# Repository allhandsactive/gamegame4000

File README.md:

# gameGame 4000
This is the *gameGame 4000*: an ESP8266-based, wifi-enabled "badge" learn-to-solder project designed for anyone who is interested in soldering on a somewhat intermediate level, or how to program these ubiquitous microcontrollers. Along with the ESP8266, it is equipped with an SSD1331 RGB OLED display, video game controller-alike buttons, and a small speaker for bleeps and bloops.  This kit is designed by *All Hands Active* (http://www.allhandsactive.org), a 501(c)(3) not-for-profit hackerspace (http://hackerspaces.org) located in Downtown Ann Arbor, MI, USA.  The included Arkanoid demo code here is based, almost verbatim, on code from the *ssd1331* library by Alexey Dynda (@lexus2k).  We added some tweaks to accommodate our unique button handling library, and adjusted pins to match our OLED screen setup.

As any good hackerspace should, we encourage people to fully tinker with the code and designs, and to find novel uses for this project.  We'd love to hear of your projects using our badge -- please get in contact with us if you'd like to share your project!

Since it is based on the same processor, much of this documentation is copied over from our last kit, the *mktwo* badge (https://github.com/allhandsactive/mktwo-badge/blob/master/README.md)

# Build instructions on Imgur
Heads up! There are a few errors in the assembly pictures at the imgur link here.  Please follow the instructions in the captions first and foremost: https://imgur.com/gallery/5YhMqiV

### **Kit parts list**

Make sure you have the following in your kit:

1x gameGame 4000 PCB

1x ESP8266 12E or 12F microprocessor

1x SSD1331 OLED display

1x 3-AA battery holder

1x Female battery connector lead with pigtail

1x Male battery connector header

1x Toggle switch

1x Header 7-socket

1x Right-angle header 6-pin

1x Speaker 8-ohm 20mm

1x Linear regulator 1.2A 3.3v STMicroelectronics P/N LDL1117S33R

1x Shift register 8-bit Nexperia USA Inc. P/N 74HC597D,653

2x Electrolytic capacitor 10uF 50V

2x Ceramic capacitor 0.1uF 50V

4x Nylon standoff M2 x 12mm

4x Nylon nut M2

4x Nylon screw M2 x 5mm

10x Push button

12x Resistor 10k Ohm 1/8W 5%

### **Requirements**
#### **Hardware**
The safest and more reliable way to load firmware onto your *gameGame 4000* is with a USB-serial programming cable.  You will need to use an FTDI cable, like the FTDI cable here (https://www.sparkfun.com/products/9717) , *OR* you can use a cheaper cable with the Prolific *PL2303HX* chipset (look on eBay! We were able to easily find them from US sellers for under $5).  A serial voltage level of 3.3v for programming is recommended, but we've safely done it with 5v, too.  **NOTE:** Windows/Apple users, you will likely have to download a driver to use the *PL2303HX*.  Sorry, we can't provide support on how to do that.

Such cables hook up to the FTDI pin block near the bottom of the *gameGame 4000*.  Take care when hooking up the cable, because the FTDI pins on the badge are not keyed.  When you plug it into the badge, make sure the black wire on the FTDI cable faces toward the left side of the badge (assuming you are viewing the front of the badge).  In case your cable doesn't have a single plug, but a bunch of individual wires (like the Prolific ones), the pinout should be as follows, assuming the board is facing up toward you, left-to-right (*NC = No Connection*):

**BLACK NC NC GREEN WHITE NC**

The red wire from the programming cable should not be connected, which also means you will need to power the badge with the battery when programming it.

#### **Software**
We recommend a current version of the Arduino IDE (https://www.arduino.cc/en/Main/Software), either binary or git clone.

Under Arduino's preferences, *Additional Boards Manager URLs*, you will need to add:

`http://arduino.esp8266.com/stable/package_esp8266com_index.json`

Under *Tools|Board:|Boards Manager...* search for and install `esp8266`.
**NOTE: you will need to add the URL above in preferences first.**
You will also need some libraries to run the OLED screen.  Under *Sketch|Include Library|Manage Libraries...* search for `SSD1331`.  Any of those should work to varying degrees.  Try them out and experiment! If you want to try the included `arkanoid8-pcon` demo, grab the `ssd1306` library, which comes with some cool demo stuff for our `SSD1331` OLED screen.  Keep in mind that you will have to update the pin settings on the other demos since they are connected differently for this board.

Now restart the Arduino IDE.

### **Badge Programming**
#### **Wired Programming**
##### **SETUP**

Under the Arduino IDE settings (most of these seem to be defaults):

Board: "NodeMCU 1.0 (ESP-12E Module)"

CPU Frequency: "80 MHz"

Debug Port: "Disabled"

Debug Level: "None"

lwIP Variant: "v2 Lower Memory"

Flash Size: "4M (3M SPIFFS)"

Upload Speed: "460800" (try lowering this if you have issues while programming the board)

Port: (whatever port the programming cable is on.  In Linux, it'll be something like `/dev/ttyUSB0`)

Programmer: "AVRISP mkII"

Erase Flash: "Only Sketch"

##### **PROCEDURE**

Let's take a look at the `ssd1306` library's demo games.  After installing that library, you can load up the `arkanoid8-gamegame` code from this repo.

To upload your code, you need to put the badge into "write" or "programming" mode.  To do this, locate the `PRGM` and `RESET` buttons on the badge.  Hold the `PRGM` button. Press and release the `RESET` button. You may now release `PRGM`. **You will need to repeat this procedure before each firmware upload.**
You may now compile and upload as you would with any Arduino, using the Arduino IDE.

**NOTE: Some FTDI cables might not cause the ESP to reset after successful programming.  If you are observing this behavior, just use the** `RESET` **button on the badge.**

### Other notes
The speaker is linked to pin 5, if you wish to make bleeps and bloops with the `tone` function.

Other pin settings that might be useful:

For the OLED display:

sclk = 14

mosi = 13

cs = 2

rst = 0

dc = 16

For buttons (check out the example code in this repo):

pl/sload = 4

shcp/sck = 0

stcp/clk = 15

shift reg. serial output ("BUTTONS" on schematic) = 10

The board works great with three NiMH AA batteries.

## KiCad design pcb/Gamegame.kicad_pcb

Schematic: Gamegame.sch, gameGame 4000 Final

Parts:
BT1: Battery; PinHeader_1x02_P2.54mm_Vertical
C1, C2: 0.1uF; C_Rect_L4.6mm_W2.0mm_P2.50mm_MKS02_FKP02
C3, C4: 10uF; C_Rect_L4.6mm_W2.0mm_P2.50mm_MKS02_FKP02
J1: FTDI; PinHeader_1x06_P2.54mm_Horizontal
J2: SSD1331 SPI OLED; SD1131
LS1: Speaker; PinHeader_1x02_P2.54mm_Vertical
R1, R2, R3, R4, R5, R6, R7, R8, R9, R10, R12, R13: 10k; R_Axial_DIN0204_L3.6mm_D1.6mm_P5.08mm_Horizontal
SW1: UP; SW_PUSH_6mm
SW2: DOWN; SW_PUSH_6mm
SW3: LEFT; SW_PUSH_6mm
SW4: RIGHT; SW_PUSH_6mm
SW5: A; SW_PUSH_6mm
SW6: B; SW_PUSH_6mm
SW7: START; SW_PUSH_6mm
SW8: SELECT; SW_PUSH_6mm
SW9: RESET; SW_PUSH_6mm
SW10: PRGM; SW_PUSH_6mm
SW11: SW_SPDT; FanPinHeader_1x03_P2.54mm_Vertical
U1: 74LS597; SOIC-16_3.9x9.9mm_P1.27mm
U2: ESP-12E
U3: AP1117-33; SOT-223-3_TabPin2

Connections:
+3V3: C1.1, C2.1, C4.1, J2.2, J2.5, R9.1, R10.1, R13.2, SW1.1, SW2.1, SW3.1, SW4.1, SW5.1, SW6.1, SW7.1, SW8.1, U1.10, U1.16, U2.8 (VCC), U3.2 (VO)
+BATT: C3.1, SW11.1, U3.3 (VI)
/BUTTONS: U1.9, U2.12 (GPIO10)
/CLK: J2.3, U2.5 (GPIO14)
/CS: J2.7, R13.1, U2.17 (GPIO2)
/DC: J2.6, U2.4 (GPIO16)
/MOSI: J2.4, U2.7 (GPIO13)
/RST: R10.2, SW9.2, U2.1 (REST)
/RX: J1.4, U2.21 (RXD)
/SHCP: SW10.1, U1.11, U2.18 (GPIO0)
/SPEAKER: LS1.1, U2.20 (GPIO5)
/STCP: R12.1, U1.12, U2.16 (GPIO15)
/TX: J1.5, U2.22 (TXD)
/~PL: U1.13, U2.19 (GPIO4)
GND: BT1.2, C1.2, C2.2, C3.2, C4.2, J1.1, J2.1, LS1.2, R1.2, R2.2, R3.2, R4.2, R5.2, R6.2, R7.2, R8.2, R12.2, SW9.1, SW10.2, U1.8, U1.14, U2.15 (GND), U3.1 (GND)
unnamed: BT1.1, SW11.2
unnamed: R1.1, SW1.2, U1.15
unnamed: R2.1, SW2.2, U1.1
unnamed: R3.1, SW3.2, U1.2
unnamed: R4.1, SW4.2, U1.3
unnamed: R5.1, SW5.2, U1.4
unnamed: R6.1, SW6.2, U1.5
unnamed: R7.1, SW7.2, U1.6
unnamed: R8.1, SW8.2, U1.7
unnamed: R9.2, U2.3 (CH_PD)

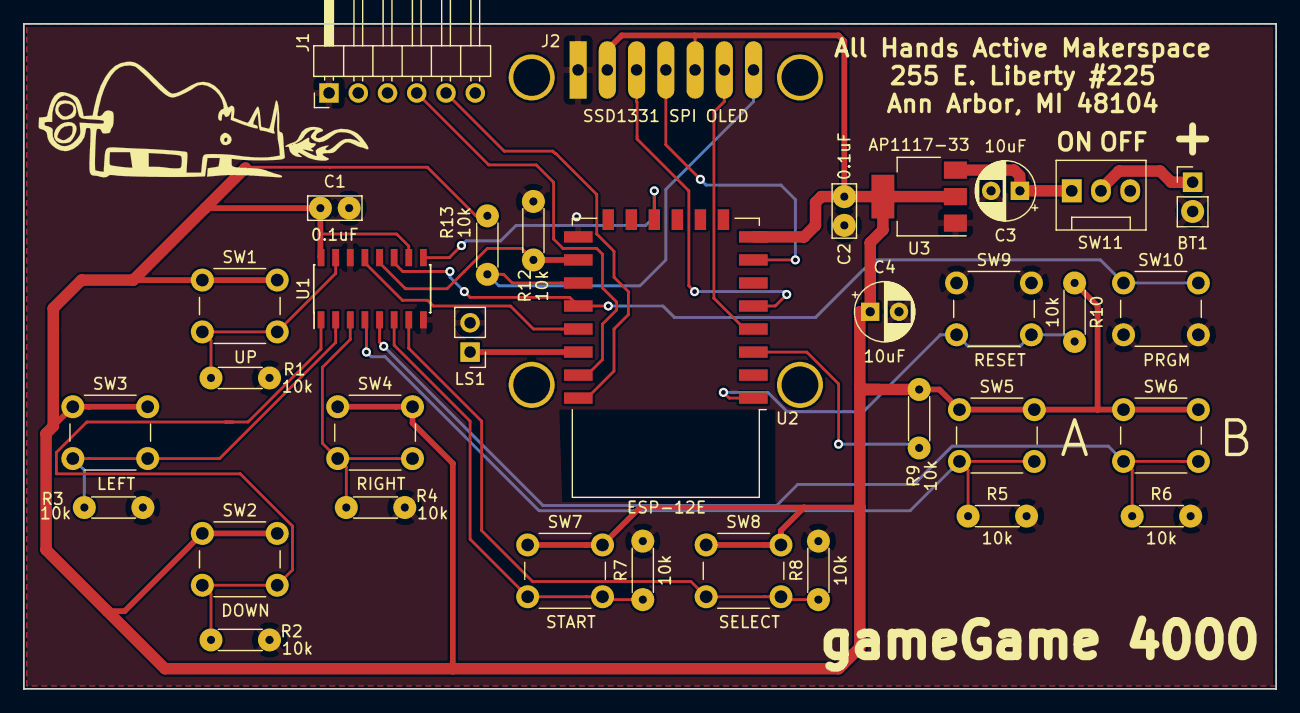
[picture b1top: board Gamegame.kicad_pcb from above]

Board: 2 copper layers, 108.8 x 57.8 mm, 34 parts (0 on the bottom side), 25 nets.

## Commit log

2018-05-05 Added buttons example, and docs directory.
2018-05-05 Adding demo code for funteims. Added schematic.
2018-05-22 added pcb files
2019-08-08 Refreshed with the latest Arkanoid code from the SSD1331 library demo.
2019-08-10 Added bleeps and bloops for HI-FI gaming enjoyment. Ported over Alexey Dynda's SSD1331 Loderunner demo, too!
